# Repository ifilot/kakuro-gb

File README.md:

# Kakuro for the Game Boy

Kakuro, the number crossword, for the Game Boy, in colour on the Game Boy
Color. There are 80 puzzles, from 6x6 to 8x8, in a 32 KiB ROM-only
cartridge without battery RAM: nothing is saved. Best times last until the
Game Boy is switched off, and a puzzle left unsolved is not kept at all.

[Play it in your browser](https://ifilot.github.io/kakuro-gb/), in the
[binjgb](https://github.com/binji/binjgb) emulator, on a Game Boy or a Game
Boy Color.

## Play

The opening screen shows the maple artwork with a blinking PRESS START.
Music begins with its fade-in; press START to choose a puzzle group.

Load `build/kakuro.gb` in an emulator (mGBA, SameBoy, BGB, ...) or on a
flash cartridge. It plays in colour on the Game Boy Color and in shades on
the others.

Fill every white cell with a digit from 1 to 9 so that each run of white
cells adds up to the sum before it: the upper-right triangle is the sum of
the run to its right, the lower-left one of the run below. No digit repeats
within a run, and grey cells are given. Every puzzle has exactly one
solution.

| Button | On the board |
| --- | --- |
| D-pad | Move to the nearest white cell in that direction |
| A | Keypad: choose 1-9 or erase (x), A to put it, B to cancel |
| B | Wipe the cell |
| SELECT | Combinations of the cursor's runs |
| START | Pause: resume, reveal the cell (+30 seconds), start over, music, quit |

The status line shows the cursor's runs (`→20/4`, `↓16/2`) and the clock.
When stuck, SELECT lists every combination that makes each sum, plus the
digits the cell can still take.

On the title screen choose a size (a row) and difficulty (a column), then
a puzzle; solved ones get a check mark. A group shows 20 puzzles a page:
move past the left or right edge for the page before or after. Nothing is saved: a puzzle is played in one go
(quitting loses it, so the game asks first), and best times last until the
Game Boy is switched off.

## Puzzles

The puzzles come from [kakuro-8bit](https://github.com/ifilot/kakuro-8bit)
(`assets/puzzles/e5`). That project also forbids two runs from using the
same set of digits; with the standard rules alone, 26 of them have more
than one solution. `tools/gen_puzzles.py` adds givens from the stored
solution (1 to 3 per puzzle) until each has exactly one.

| Grid (with the sums) | Difficulty | Puzzles |
| --- | --- | --- |
| 6 x 6 | ★★ | 10 |
| 7 x 7 | ★★ | 20 |
| 7 x 7 | ★★★ | 10 |
| 8 x 8 | ★★ | 20 |
| 8 x 8 | ★★★ | 20 |

Puzzles are numbered within their group, from 1.

A cell is 16x16 dots, so an 8x8 grid (128 dots) fits the 160x136 dots above
the status line whole. kakuro-8bit's 9x9 and 10x10 puzzles would not, and
are left out.

## Build

The game is C for [GBDK-2020](https://github.com/gbdk-2020/gbdk-2020)
(4.5.0). Nothing needs root: unpack the Linux release in your home
directory, which is where the Makefile looks by default (`GBDK_HOME`).

```sh
curl -sL https://github.com/gbdk-2020/gbdk-2020/releases/download/4.5.0/gbdk-linux64.tar.gz | tar xz -C ~
make                  # -> build/kakuro.gb, and the ROM space used
```

The opening artwork alone uses ZX0 compression. `make gfx` uses the
`gbcompress` tool bundled with GBDK and verifies both compressed streams
by decompressing them again. The game expands the tiles and map directly
into video memory while the display is off, without an image buffer in RAM.

`make run` plays it in [mGBA](https://mgba.io) (`sudo apt install mgba-qt`;
`MGBA=` names another binary). The tests and screenshots use
[PyBoy](https://github.com/Baekalfen/PyBoy):

```sh
python3 -m venv ~/.venvs/pyboy && ~/.venvs/pyboy/bin/pip install pyboy pillow
make test PYTHON=~/.venvs/pyboy/bin/python
```

| Target | |
| --- | --- |
| `make` | Build `build/kakuro.gb` |
| `make run` | Play in mGBA (arrows; A = `x`, B = `z`, START = Return, SELECT = Backspace) |
| `make test` | Every puzzle solved in the emulator, see below |
| `make screenshots` | Every screen -> `build/screens/` |
| `make docs` | The pictures above, in Game Boy green -> `docs/` |
| `make sticker` | Printable cartridge label -> `assets/cartridge/` (requires `rsvg-convert`) |
| `make sticker-zen` | Five illustrated labels with a verified puzzle -> `assets/cartridge/zen-v2/` |
| `make puzzles` | Regenerate `src/puzzles.[ch]` from `assets/puzzles` |
| `make gfx` | Regenerate `src/gfx.[ch]`; tile sheet in `build/gfx_preview.png` |
| `make music` | Regenerate `src/music.[ch]` from the notes in `tools/gen_music.py` |
| `make listen` | The music as PyBoy plays it -> `build/music.wav` |
| `make site` | The website, the game in the browser -> `_site/` (checked) |
| `make serve` | The website at http://localhost:8000 |

Every push, to any branch, builds the ROM and runs `make test`
(`.github/workflows/build.yml`); a tag `v<version>`, matching
`src/version.h`, also publishes a release with the ROM, a zip and that
version's CHANGELOG section. Every push to `master` builds the website and
deploys it to GitHub Pages (`.github/workflows/pages.yml`); Pages must use
GitHub Actions as its source.

## License

GNU General Public License v3.0; see [LICENSE](LICENSE).

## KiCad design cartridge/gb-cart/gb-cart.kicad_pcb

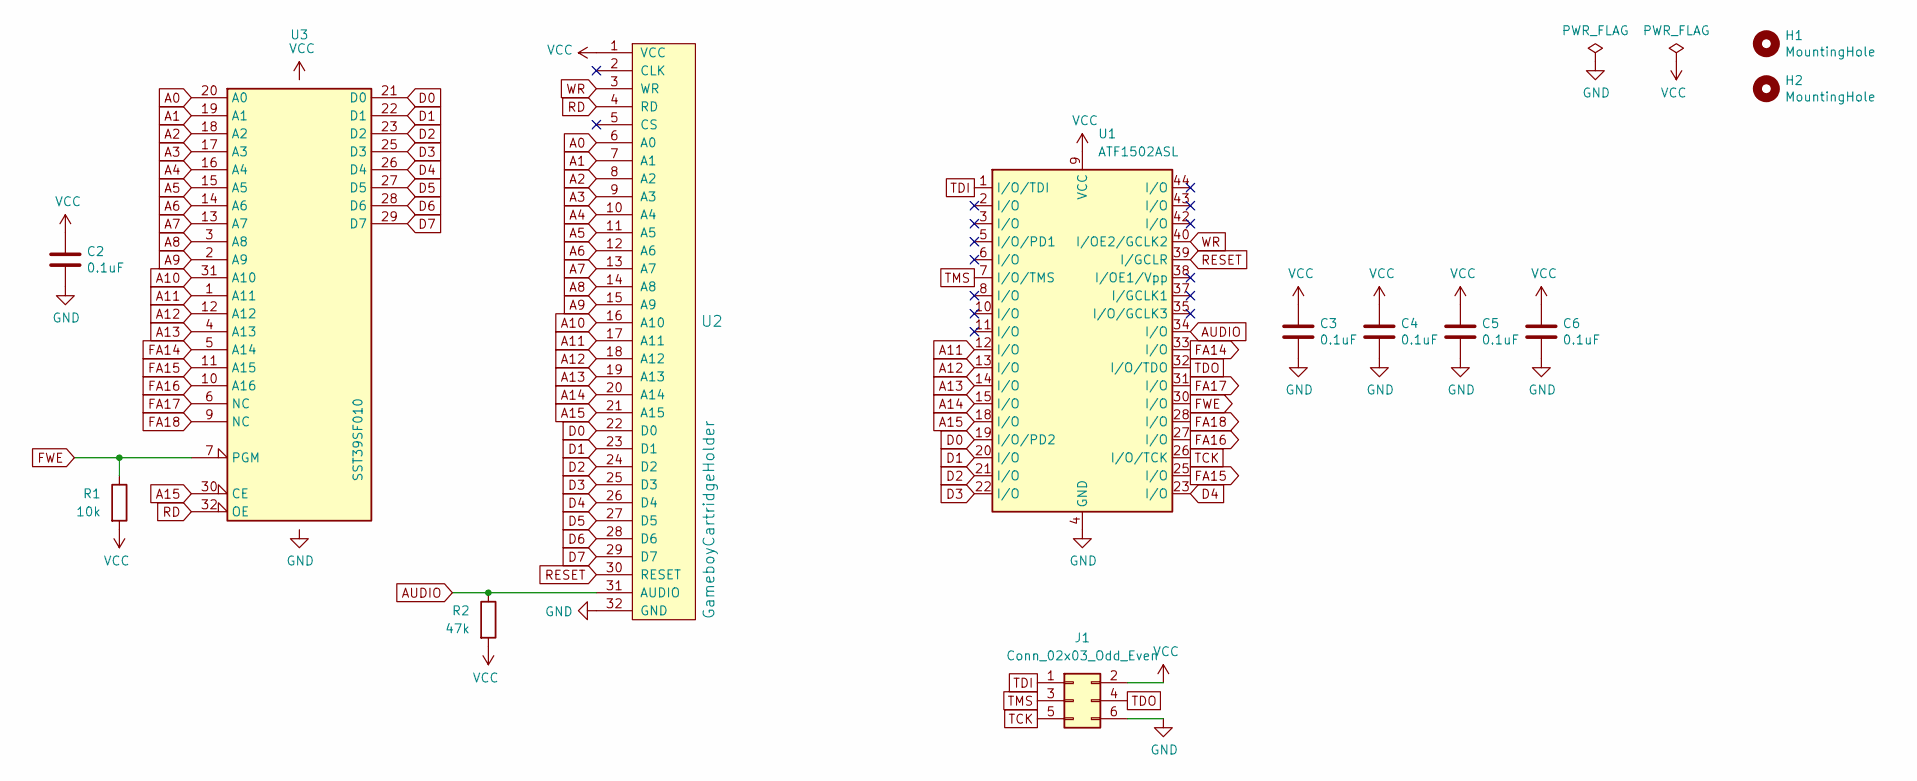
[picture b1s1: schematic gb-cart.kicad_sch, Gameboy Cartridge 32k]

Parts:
C2, C3, C4, C5, C6: 0.1uF; C_0805_2012Metric_Pad1.18x1.45mm_HandSolder
H1: MountingHole; MountingHole_7.2mm
H2: MountingHole; MountingHole_2.3mm
J1: Conn_02x03_Odd_Even; PinSocket_2x03_P2.54mm_Vertical
R1: 10k; R_0805_2012Metric_Pad1.20x1.40mm_HandSolder
R2: 47k; R_0805_2012Metric_Pad1.20x1.40mm_HandSolder
U1: ATF1502ASL; TQFP-44_10x10mm_P0.8mm
U2: GameboyCartridgeHolder; GameBoy_Cartridge_1x32_P1.50mm_Edge
U3: SST39SF010; TSOP-I-32_11.8x8mm_P0.5mm

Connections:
A0: U2.6 (A0), U3.20 (A0)
A1: U2.7 (A1), U3.19 (A1)
A2: U2.8 (A2), U3.18 (A2)
A3: U2.9 (A3), U3.17 (A3)
A4: U2.10 (A4), U3.16 (A4)
A5: U2.11 (A5), U3.15 (A5)
A6: U2.12 (A6), U3.14 (A6)
A7: U2.13 (A7), U3.13 (A7)
A8: U2.14 (A8), U3.3 (A8)
A9: U2.15 (A9), U3.2 (A9)
A10: U2.16 (A10), U3.31 (A10)
A11: U1.12 (I/O), U2.17 (A11), U3.1 (A11)
A12: U1.13 (I/O), U2.18 (A12), U3.12 (A12)
A13: U1.14 (I/O), U2.19 (A13), U3.4 (A13)
A14: U1.15 (I/O), U2.20 (A14)
A15: U1.18 (I/O), U2.21 (A15), U3.30 (CE)
AUDIO: R2.1, U1.34 (I/O), U2.31 (AUDIO)
D0: U1.19 (I/O/PD2), U2.22 (D0), U3.21 (D0)
D1: U1.20 (I/O), U2.23 (D1), U3.22 (D1)
D2: U1.21 (I/O), U2.24 (D2), U3.23 (D2)
D3: U1.22 (I/O), U2.25 (D3), U3.25 (D3)
D4: U1.23 (I/O), U2.26 (D4), U3.26 (D4)
D5: U2.27 (D5), U3.27 (D5)
D6: U2.28 (D6), U3.28 (D6)
D7: U2.29 (D7), U3.29 (D7)
FA14: U1.33 (I/O), U3.5 (A14)
FA15: U1.25 (I/O), U3.11 (A15)
FA16: U1.27 (I/O), U3.10 (A16)
FA17: U1.31 (I/O), U3.6 (NC)
FA18: U1.28 (I/O), U3.9 (NC)
FWE: R1.1, U1.30 (I/O), U3.7 (PGM)
GND: C2.2, C3.2, C4.2, C5.2, C6.2, J1.6, U1.4 (GND), U1.16 (GND), U1.24 (GND), U1.36 (GND), U2.32 (GND), U3.24 (GND)
RD: U2.4 (RD), U3.32 (OE)
RESET: U1.39 (I/GCLR), U2.30 (RESET)
TCK: J1.5, U1.26 (I/O/TCK)
TDI: J1.1, U1.1 (I/O/TDI)
TDO: J1.4, U1.32 (I/O/TDO)
TMS: J1.3, U1.7 (I/O/TMS)
VCC: C2.1, C3.1, C4.1, C5.1, C6.1, J1.2, R1.2, R2.2, U1.9 (VCC), U1.17 (VCC), U1.29 (VCC), U1.41 (VCC), U2.1 (VCC), U3.8 (VCC)
WR: U1.40 (I/OE2/GCLK2), U2.3 (WR)

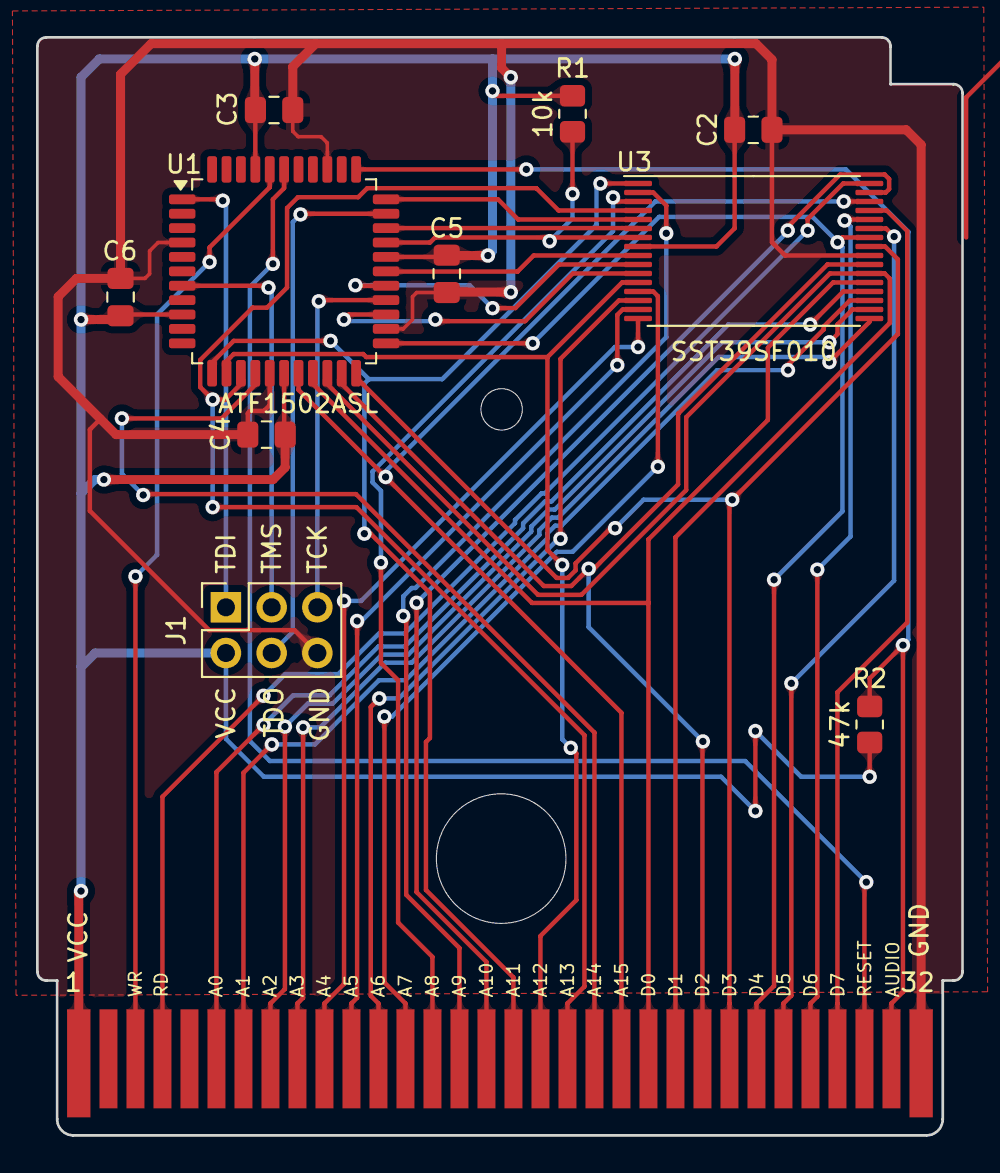
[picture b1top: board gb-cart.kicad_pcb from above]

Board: 2 copper layers, 51.4 x 61.0 mm, 13 parts (0 on the bottom side), 40 nets.

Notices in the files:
README.md:
License: GPL v3
